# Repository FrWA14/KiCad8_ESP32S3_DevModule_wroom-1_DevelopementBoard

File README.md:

Contient tout le projet KiCad afin de faire une carte de développement ESP32 :

-Schématique
-PCB
-BOM et référence JLCPCB

/!\ Il faudra faire la rotation de certains composants lors de la production chez JLCPCB.

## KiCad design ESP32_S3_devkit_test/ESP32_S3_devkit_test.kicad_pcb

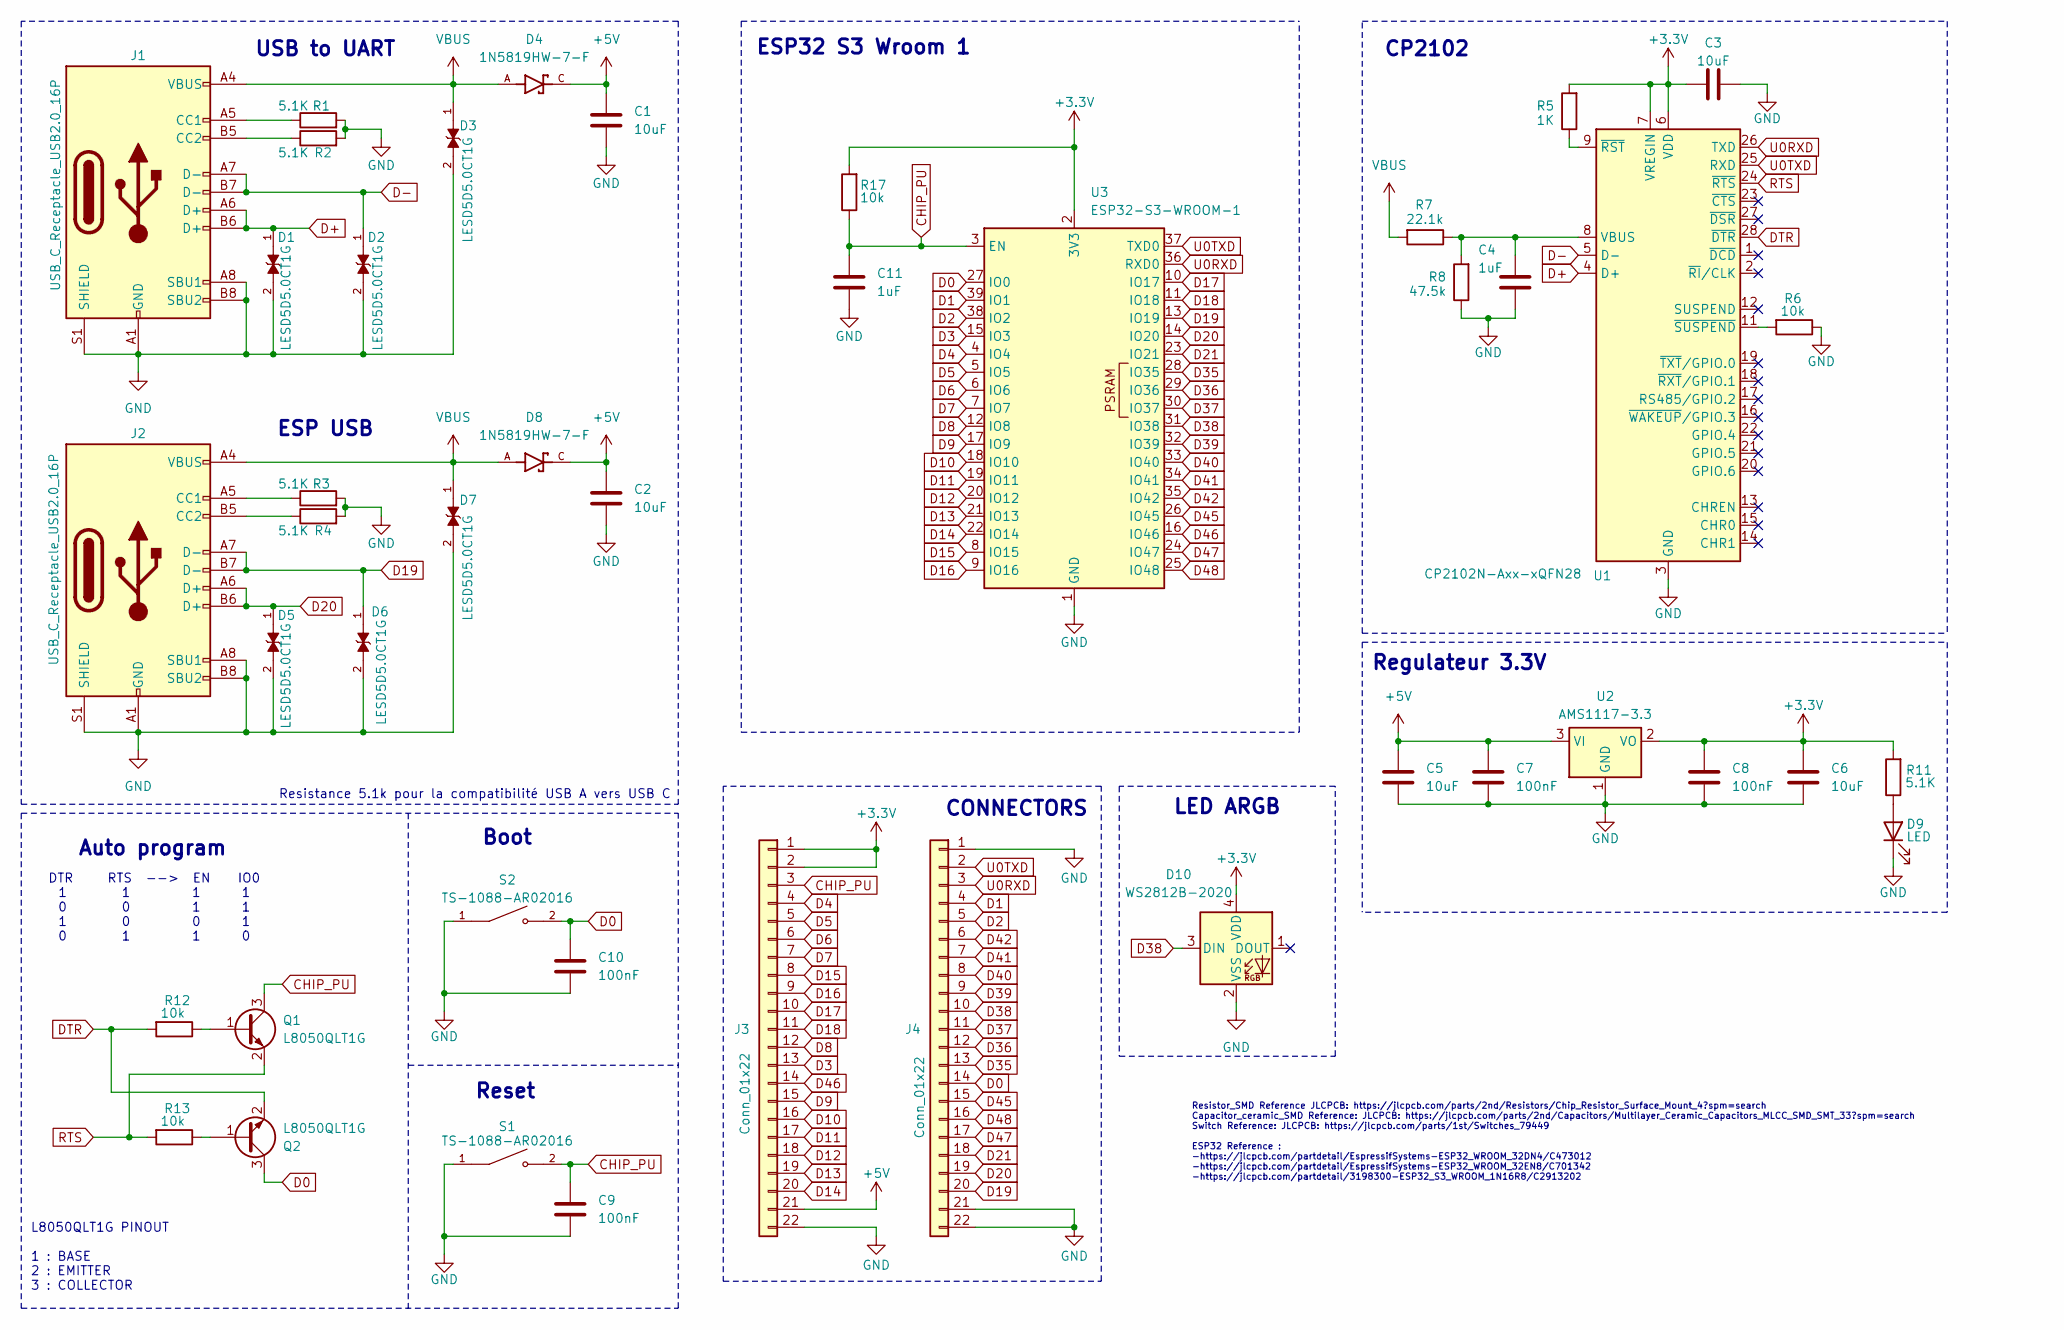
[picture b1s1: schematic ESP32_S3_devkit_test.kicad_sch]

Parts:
C1, C2, C3, C5, C6: 10uF; C_0603_1608Metric; JLCPCB Part # C1691
C4, C11: 1uF; C_0603_1608Metric; JLCPCB Part # C15849
C7, C8, C9, C10: 100nF; C_0603_1608Metric; JLCPCB Part # C14663
D1, D2, D3, D5, D6, D7: LESD5D5.0CT1G; D_SOD-523_LESD5D5.0CT1G; PARTREV O; JLCPCB Part # C383211
D4, D8: 1N5819HW-7-F; D_SOD-123_1N5819HW-7-F; PARTREV 18-2; JLCPCB Part # C82544
D9: LED; LED_0603_1608Metric; JLCPCB Part # C965799
D10: WS2812B-2020; LED_WS2812B-2020_PLCC4_2.0x2.0mm; JLCPCB Part # C965555
J1, J2: USB_C_Receptacle_USB2.0_16P; USB_C_Receptacle_HCTL_HC-TYPE-C-16P-01A; JLCPCB Part # C393939
J3, J4: Conn_01x22; PinHeader_1x22_P2.54mm_Vertical; JLCPCB Part # C20610289
Q1, Q2: L8050QLT1G; SOT-23; JLCPCB Part # C49581
R1, R2, R3, R4, R11: 5.1K; R_0603_1608Metric; JLCPCB Part # C23186
R5: 1K; R_0603_1608Metric; JLCPCB Part # C21190
R6, R12, R13, R17: 10k; R_0603_1608Metric; JLCPCB Part # C25804
R7: 22.1k; R_0603_1608Metric; JLCPCB Part # C25961
R8: 47.5k; R_0603_1608Metric; JLCPCB Part # C23061
S1, S2: TS-1088-AR02016; SW_TS-1088-AR02016; PARTREV N/A; JLCPCB Part # C720477
U1: CP2102N-Axx-xQFN28; QFN-28-1EP_5x5mm_P0.5mm_EP3.35x3.35mm; JLCPCB Part # C964632
U2: AMS1117-3.3; SOT-223-3_TabPin2; JLCPCB Part # C6186
U3: ESP32-S3-WROOM-1; JLCPCB Part # C2913202

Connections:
+3.3V: C3.1, C6.1, C8.1, D10.4 (VDD), J3.1, J3.2, R5.2, R11.2, R17.2, U1.6 (VDD), U1.7 (VREGIN), U2.2 (VO), U3.2 (3V3)
+5V: C1.1, C2.1, C5.1, C7.1, D4.C, D8.C, J3.21, U2.3 (VI)
CHIP_PU: C9.1, C11.1, J3.3, Q1.3 (C), R17.1, S1.2, U3.3 (EN)
D0: C10.1, J4.14, Q2.3 (C), S2.2, U3.27 (IO0)
D1: J4.4, U3.39 (IO1)
D2: J4.5, U3.38 (IO2)
D3: J3.13, U3.15 (IO3)
D4: J3.4, U3.4 (IO4)
D5: J3.5, U3.5 (IO5)
D6: J3.6, U3.6 (IO6)
D7: J3.7, U3.7 (IO7)
D8: J3.12, U3.12 (IO8)
D9: J3.15, U3.17 (IO9)
D10: J3.16, U3.18 (IO10)
D11: J3.17, U3.19 (IO11)
D12: J3.18, U3.20 (IO12)
D13: J3.19, U3.21 (IO13)
D14: J3.20, U3.22 (IO14)
D15: J3.8, U3.8 (IO15)
D16: J3.9, U3.9 (IO16)
D17: J3.10, U3.10 (IO17)
D18: J3.11, U3.11 (IO18)
D19: D6.1, J2.A7 (D-), J2.B7 (D-), J4.20, U3.13 (IO19)
D20: D5.1, J2.A6 (D+), J2.B6 (D+), J4.19, U3.14 (IO20)
D21: J4.18, U3.23 (IO21)
D35: J4.13, U3.28 (IO35)
D36: J4.12, U3.29 (IO36)
D37: J4.11, U3.30 (IO37)
D38: D10.3 (DIN), J4.10, U3.31 (IO38)
D39: J4.9, U3.32 (IO39)
D40: J4.8, U3.33 (IO40)
D41: J4.7, U3.34 (IO41)
D42: J4.6, U3.35 (IO42)
D45: J4.15, U3.26 (IO45)
D46: J3.14, U3.16 (IO46)
D47: J4.17, U3.24 (IO47)
D48: J4.16, U3.25 (IO48)
D+: D1.1, J1.A6 (D+), J1.B6 (D+), U1.4 (D+)
D-: D2.1, J1.A7 (D-), J1.B7 (D-), U1.5 (D-)
DTR: Q2.2 (E), R12.2, U1.28 (~DTR)
GND: C1.2, C2.2, C3.2, C4.2, C5.2, C6.2, C7.2, C8.2, C9.2, C10.2, C11.2, D1.2, D2.2, D3.2, D5.2, D6.2, D7.2, D9.1 (K), D10.2 (VSS), J1.A1 (GND), J1.A8 (SBU1), J1.A12 (GND), J1.B1 (GND), J1.B8 (SBU2), J1.B12 (GND), J1.S1 (SHIELD), J2.A1 (GND), J2.A8 (SBU1), J2.A12 (GND), J2.B1 (GND), J2.B8 (SBU2), J2.B12 (GND), J2.S1 (SHIELD), J3.22, J4.1, J4.21, J4.22, R1.2, R2.2, R3.2, R4.2, R6.1, R8.1, S1.1, S2.1, U1.3 (GND), U1.29 (GND), U2.1 (GND), U3.1 (GND), U3.40 (GND), U3.41 (GND)
unnamed: D9.2 (A), R11.1
unnamed: J1.A5 (CC1), R1.1
unnamed: J1.B5 (CC2), R2.1
unnamed: J2.A5 (CC1), R3.1
unnamed: J2.B5 (CC2), R4.1
unnamed: Q1.1 (B), R12.1
unnamed: Q2.1 (B), R13.1
unnamed: C4.1, R7.1, R8.2, U1.8 (VBUS)
unnamed: R5.1, U1.9 (~RST)
unnamed: R6.2, U1.11 (~SUSPEND)
RTS: Q1.2 (E), R13.2, U1.24 (~RTS)
U0RXD: J4.3, U1.26 (TXD), U3.36 (RXD0)
U0TXD: J4.2, U1.25 (RXD), U3.37 (TXD0)
VBUS: D3.1, D4.A, D7.1, D8.A, J1.A4 (VBUS), J1.A9 (VBUS), J1.B4 (VBUS), J1.B9 (VBUS), J2.A4 (VBUS), J2.A9 (VBUS), J2.B4 (VBUS), J2.B9 (VBUS), R7.2

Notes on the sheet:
LED ARGB
Resistor_SMD Reference JLCPCB: https://jlcpcb.com/parts/2nd/Resistors/Chip_Resistor_Surface_Mount_4?spm=search Capacitor_ceramic_SMD Reference: JLCPCB: https://jlcpcb.com/parts/2nd/Capacitors/Multilayer_Ceramic_Capacitors_MLCC_SMD_SMT_33?spm=search Switch Reference: JLCPCB: https://jlcpcb.com/parts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
ESP USB
Reset
Resistance 5.1k pour la compatibilité USB A vers USB C
L8050QLT1G PINOUT 1 : BASE 2 : EMITTER 3 : COLLECTOR
CONNECTORS
DTR RTS --> EN IO0 1 1 1 1 0 0 1 1 1 0 0 1 0 1 1 0
USB to UART
Boot
Regulateur 3.3V
Auto program
CP2102
ESP32 S3 Wroom 1

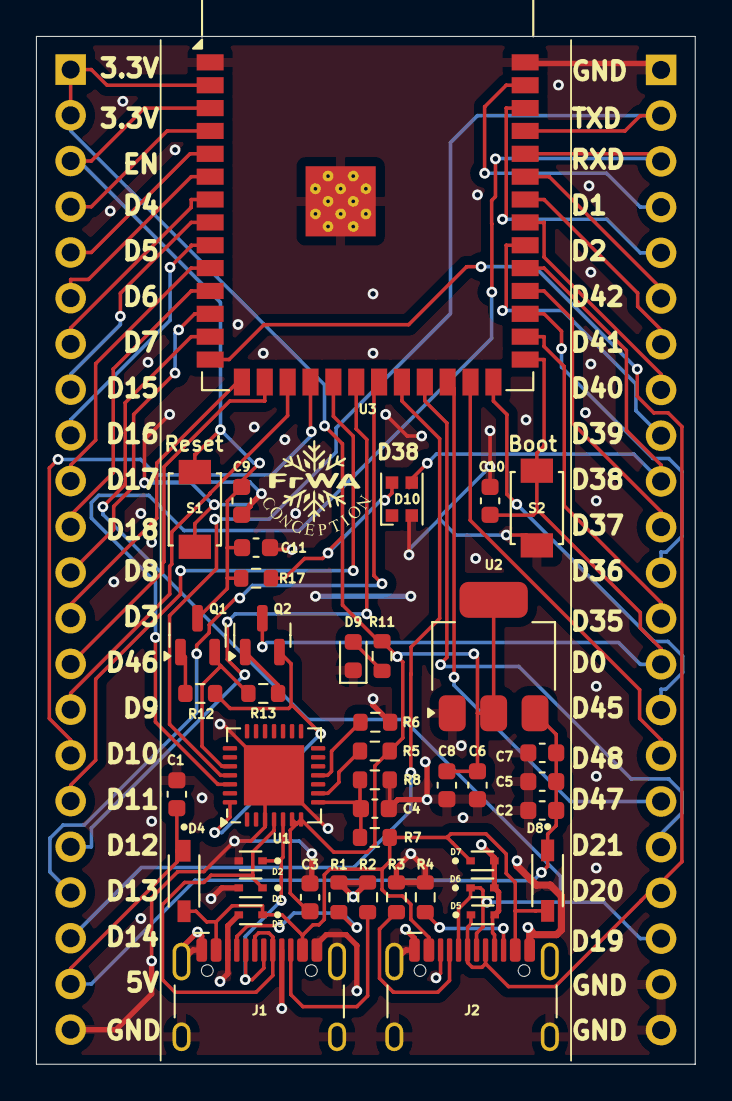
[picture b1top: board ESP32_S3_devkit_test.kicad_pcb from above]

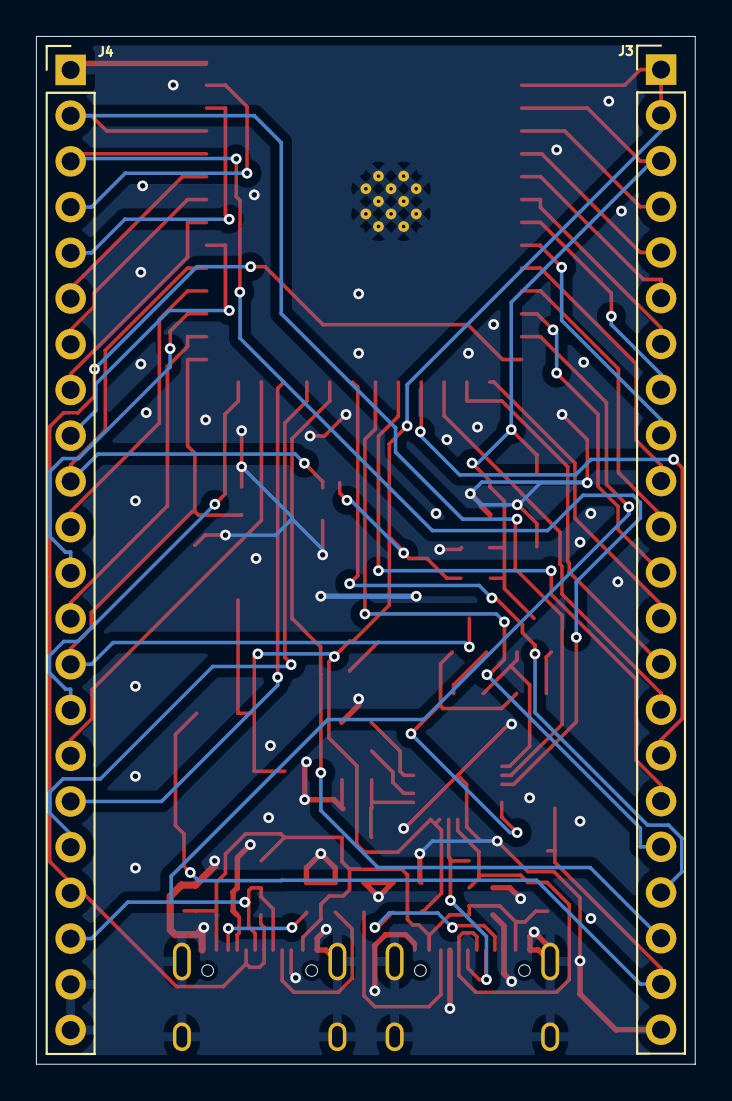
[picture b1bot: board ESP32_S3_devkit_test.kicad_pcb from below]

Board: 2 copper layers, 36.6 x 57.1 mm, 44 parts (2 on the bottom side), 55 nets.

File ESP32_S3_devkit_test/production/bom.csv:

Designator,Footprint,Quantity,Value,LCSC Part #
"C1, C2, C3, C5, C6",0603,5,10uF,C1691
"C10, C7, C8, C9",0603,4,100nF, C14663
"C11, C4",0603,2,1uF,C15849
"D1, D2, D3, D5, D6, D7",D_SOD-523_LESD5D5.0CT1G,6,LESD5D5.0CT1G,C383211
D10,LED_WS2812B-2020_PLCC4_2.0x2.0mm,1,WS2812B-2020,C965555
"D4, D8",D_SOD-123_1N5819HW-7-F,2,1N5819HW-7-F, C82544
D9,0603,1,LED, C965799
"J1, J2",USB_C_Receptacle_HCTL_HC-TYPE-C-16P-01A,2,USB_C_Receptacle_USB2.0_16P,C393939
"J3, J4",PinHeader_1x22_P2.54mm_Vertical,2,Conn_01x22, C20610289
"Q1, Q2",SOT-23,2,L8050QLT1G,C49581
"R1, R11, R2, R3, R4",0603,5,5.1K,C23186
"R12, R13, R17, R6",0603,4,10k, C25804
R5,0603,1,1K,C21190
R7,0603,1,22.1k, C25961
R8,0603,1,47.5k,C23061
"S1, S2",SW_TS-1088-AR02016,2,TS-1088-AR02016,C720477
U1,QFN-28-1EP_5x5mm_P0.5mm_EP3.35x3.35mm,1,CP2102N-Axx-xQFN28,C964632
U2,SOT-223-3_TabPin2,1,AMS1117-3.3,C6186
U3,ESP32-S3-WROOM-1,1,ESP32-S3-WROOM-1,C2913202
